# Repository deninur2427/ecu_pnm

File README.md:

# PNM Engine Control Planning

Custom Engine Control Unit for LPG

## Planning

- [X] Ngobrol Rencana

### Input

- [ ] Crankshaft Position Sensor
    - [ ] Pasang Gigi. Rencana Penempatan 12-1 Crank Tooth:

    - [ ] Cetak Crank Teeth 12-1. Diameter Poros 22mm. Contoh:

    - [ ] Alternatif akrilik. Desain (tebal 2mm atau 3mm) untuk 24-1:

    - [ ] Pasang Sensor Gigi. Rencana Sensor: Opto Interruptor: [Tokopedia](https://www.tokopedia.com/xurve-store/fc-03-ir-infrared-speed-kecepatan-sensor-photo-opto-interruptor)

- [ ] Trottle Position Sensor
    - [ ] Pemasangan. Dimana dekat mesin karena tidak terkoneksi dengan mekanik intake
    - [ ] Pembelian Sensor TPS: [Tokopedia](https://www.tokopedia.com/primacave/terbaru-sensor-tps-throttle-position-sensor-beat-fi-vario-125-thalland)

- [ ] Optimasi
    - [ ] Sensor Temperature (Tentative)
    - [ ] CO2 Sensor. Rencana [Tokopedia](https://www.tokopedia.com/amanahotopart/sensor-oxygen-honda-jazz-city-belakang-oksigen-co2-o2-copotan-asli-ori)

### Output

- [ ] Intake
    - [ ] Injector. Rencana [Tokopedia](https://www.tokopedia.com/sumahonda/injector-assy-fuel-pcx-150-k97-vario-150-esp-16450k59a11)
    - [ ] Pemasangan depan Inlet tanpa klep pengatur udara:

- [ ] Spark Plug
    - [ ] Coil. Rencana [Tokopedia](https://www.tokopedia.com/lestarimotor2/coil-koil-scoopy-esp-scoopy-fi-injeksi-30510-k16-a01-asli-ahm)
    - [ ] Cop Busi [Tokopedia](https://www.tokopedia.com/azkamotor99/canglong-tutup-cop-busi-grand-supra-x-x-125-legenda-revo-kharisma)
    - [ ] Plug telah tersedia

- [ ] Aki. Alternator dan Kiprok tidak ada di Mesin
    - [x] Charger Aki tersedia
    - [ ] Jepit Aki dan Wiring nya

### PCB

- [ ] Drafting
    - [ ] Single Cylinder
        - [ ] Standalone PCB
        - [x] Nucleo Based
            - [x] F103RB

- [x] Rencana Anggaran Total

### Update Kegiatan

- Tanggal 31 Juli 2023: [Catatan](https://github.com/deninur2427/ecu_pnm/blob/main/docs/notes/tes_31072023.md)
- Tanggal 24 Agustus 2023: [Catatan](https://github.com/deninur2427/ecu_pnm/blob/main/docs/notes/tes_24082023.md)
- Tanggal 19 September 2023: [Catatan](https://github.com/deninur2427/ecu_pnm/blob/main/docs/notes/tes_19092023.md)

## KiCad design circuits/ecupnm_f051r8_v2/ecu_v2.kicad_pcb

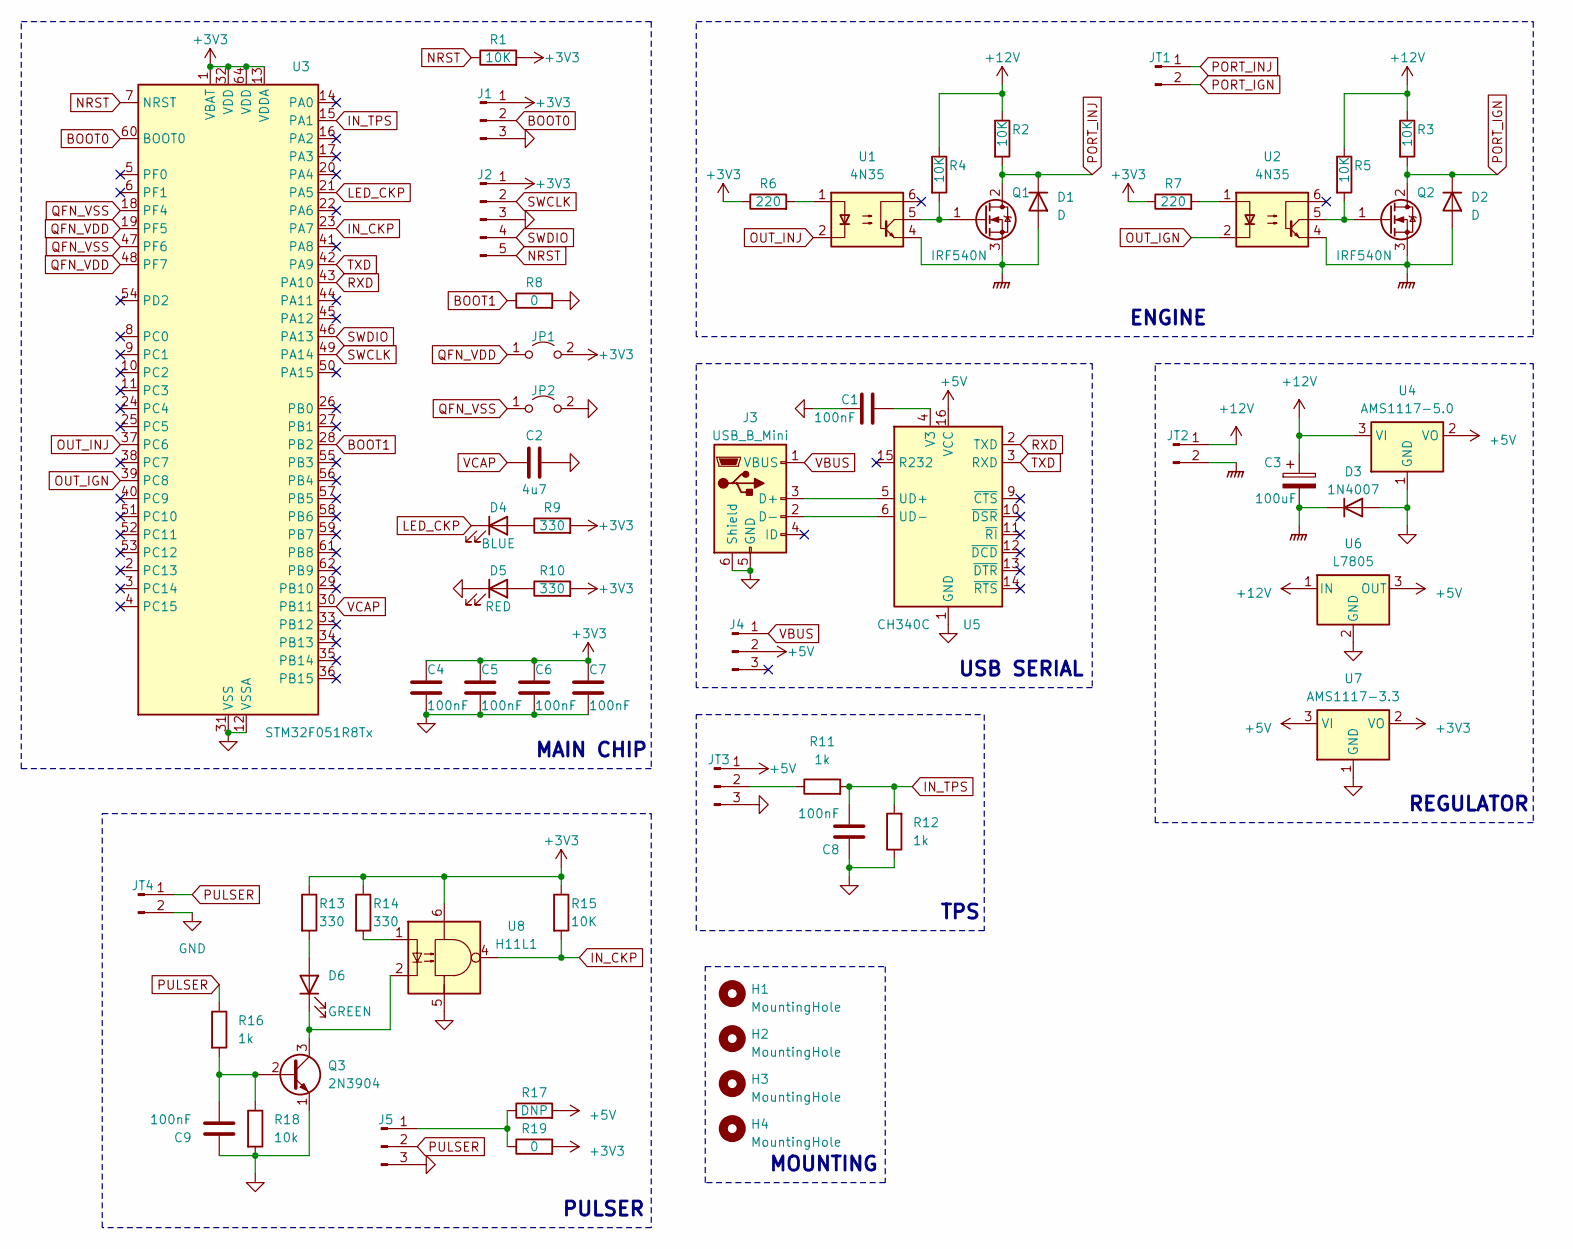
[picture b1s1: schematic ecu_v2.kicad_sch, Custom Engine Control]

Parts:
C1, C4, C5, C6, C7, C8, C9: 100nF; C_0805_2012Metric_Pad1.18x1.45mm_HandSolder
C2: 4u7; C_0805_2012Metric_Pad1.18x1.45mm_HandSolder
C3: 100uF; CP_Radial_D4.0mm_P2.00mm
D1, D2: D; D_DO-15_P10.16mm_Horizontal
D3: 1N4007; D_DO-41_SOD81_P10.16mm_Horizontal
D4: BLUE; LED_0805_2012Metric_Pad1.15x1.40mm_HandSolder
D5: RED; LED_0805_2012Metric_Pad1.15x1.40mm_HandSolder
D6: GREEN; LED_0805_2012Metric_Pad1.15x1.40mm_HandSolder
H1, H2, H3, H4: MountingHole; MountingHole_2.2mm_M2
J1, J4, J5: Conn_01x03_Pin; PinHeader_1x03_P2.54mm_Vertical
J2: Conn_01x05_Pin; PinHeader_1x05_P2.54mm_Vertical
J3: USB_B_Mini; USB_Mini-B_Wuerth_65100516121_Horizontal
JP1, JP2: Jumper_2_Open; SolderJumper-2_P1.3mm_Open_RoundedPad1.0x1.5mm
JT1, JT2, JT4: Conn_01x02_Pin; TerminalBlock_Altech_AK300-2_P5.00mm
JT3: Conn_01x03_Pin; TerminalBlock_Altech_AK300-3_P5.00mm
Q1, Q2: IRF540N; TO-220-3_Vertical
Q3: 2N3904; TO-92_Inline
R1, R2, R3, R4, R5, R15: 10K; R_0805_2012Metric_Pad1.20x1.40mm_HandSolder
R6, R7: 220; R_0805_2012Metric_Pad1.20x1.40mm_HandSolder
R8, R19: 0; R_0805_2012Metric_Pad1.20x1.40mm_HandSolder
R9, R10, R13, R14: 330; R_0805_2012Metric_Pad1.20x1.40mm_HandSolder
R11, R12, R16: 1k; R_0805_2012Metric_Pad1.20x1.40mm_HandSolder
R17: DNP; R_0805_2012Metric_Pad1.20x1.40mm_HandSolder
R18: 10k; R_0805_2012Metric_Pad1.20x1.40mm_HandSolder
U1, U2: 4N35; DIP-6_W7.62mm
U3: STM32F051R8Tx; LQFP-64_10x10mm_P0.5mm
U4: AMS1117-5.0; SOT-223-3_TabPin2
U5: CH340C; SOIC-16_3.9x9.9mm_P1.27mm
U6: L7805; TO-220-3_Vertical
U7: AMS1117-3.3; SOT-223-3_TabPin2
U8: H11L1; DIP-6_W7.62mm

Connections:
+3V3: C4.1, C5.1, C6.1, C7.1, J1.1, J2.1, JP1.2 (B), R1.2, R6.1, R7.1, R9.2, R10.2, R13.1, R14.1, R15.1, R19.2, U3.1 (VBAT), U3.13 (VDDA), U3.32 (VDD), U3.64 (VDD), U7.2 (VO), U8.6
+5V: J4.2, JT3.1, R17.2, U4.2 (VO), U5.16 (VCC), U6.3 (OUT), U7.3 (VI)
+12V: C3.1, JT2.1, R2.1, R3.1, R4.1, R5.1, U4.3 (VI), U6.1 (IN)
BOOT0: J1.2, U3.60 (BOOT0)
BOOT1: R8.1, U3.28 (PB2)
GND: C1.2, C2.2, C4.2, C5.2, C6.2, C7.2, C8.1, C9.1, D3.2 (A), D5.1 (K), J1.3, J2.3, J3.5 (GND), J3.6 (Shield), J5.3, JP2.2 (B), JT3.3, JT4.2, Q3.1 (E), R8.2, R12.1, R18.2, U3.12 (VSSA), U3.31 (VSS), U3.63 (VSS), U4.1 (GND), U5.1 (GND), U6.2 (GND), U7.1 (GND), U8.5
GNDPWR: C3.2, D1.2 (A), D2.2 (A), D3.1 (K), JT2.2, Q1.3 (S), Q2.3 (S), U1.4, U2.4
IN_CKP: R15.2, U3.23 (PA7), U8.4
IN_TPS: C8.2, R11.2, R12.2, U3.15 (PA1)
LED_CKP: D4.1 (K), U3.21 (PA5)
NRST: J2.5, R1.1, U3.7 (NRST)
unnamed: D4.2 (A), R9.1
unnamed: D5.2 (A), R10.1
unnamed: D6.2 (A), R13.2
unnamed: D6.1 (K), Q3.3 (C), U8.2
unnamed: J3.3 (D+), U5.5 (UD+)
unnamed: J3.2 (D-), U5.6 (UD-)
unnamed: J5.1, R17.1, R19.1
unnamed: JT3.2, R11.1
unnamed: Q1.1 (G), R4.2, U1.5
unnamed: Q2.1 (G), R5.2, U2.5
unnamed: C9.2, Q3.2 (B), R16.2, R18.1
unnamed: R6.2, U1.1
unnamed: R7.2, U2.1
unnamed: R14.2, U8.1
unnamed: C1.1, U5.4 (V3)
OUT_IGN: U2.2, U3.39 (PC8)
OUT_INJ: U1.2, U3.37 (PC6)
PORT_IGN: D2.1 (K), JT1.2, Q2.2 (D), R3.2
PORT_INJ: D1.1 (K), JT1.1, Q1.2 (D), R2.2
PULSER: J5.2, JT4.1, R16.1
QFN_VDD: JP1.1 (A), U3.19 (PF5), U3.48 (PF7)
QFN_VSS: JP2.1 (A), U3.18 (PF4), U3.47 (PF6)
RXD: U3.43 (PA10), U5.2 (TXD)
SWCLK: J2.2, U3.49 (PA14)
SWDIO: J2.4, U3.46 (PA13)
TXD: U3.42 (PA9), U5.3 (RXD)
VBUS: J3.1 (VBUS), J4.1
VCAP: C2.1, U3.30 (PB11)

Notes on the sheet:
REGULATOR
ENGINE
MAIN CHIP
TPS
PULSER
MOUNTING
USB SERIAL

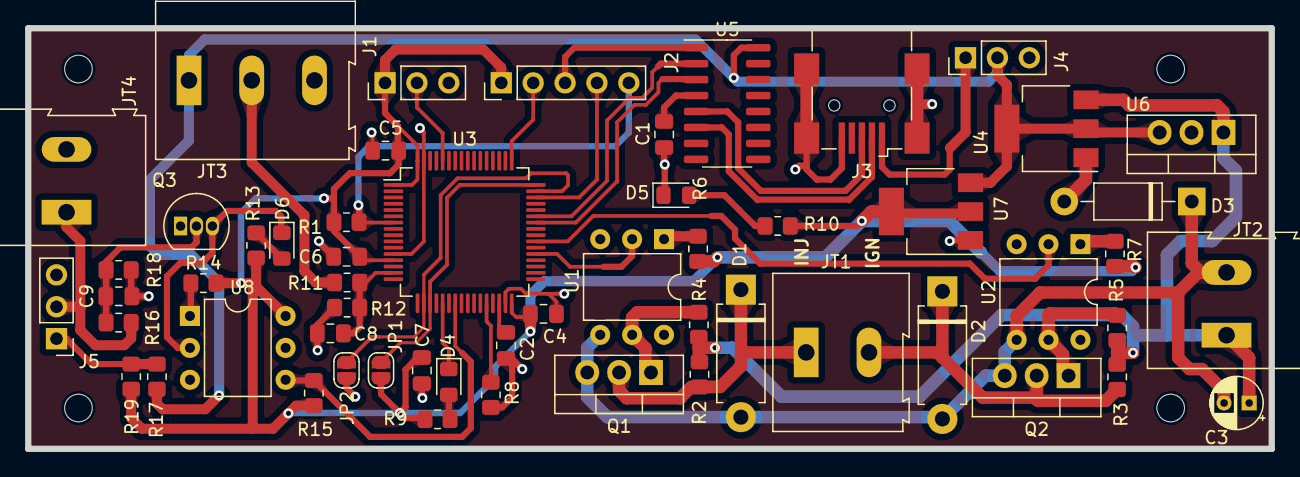
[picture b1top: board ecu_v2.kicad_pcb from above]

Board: 2 copper layers, 99.1 x 33.5 mm, 60 parts (0 on the bottom side), 39 nets.

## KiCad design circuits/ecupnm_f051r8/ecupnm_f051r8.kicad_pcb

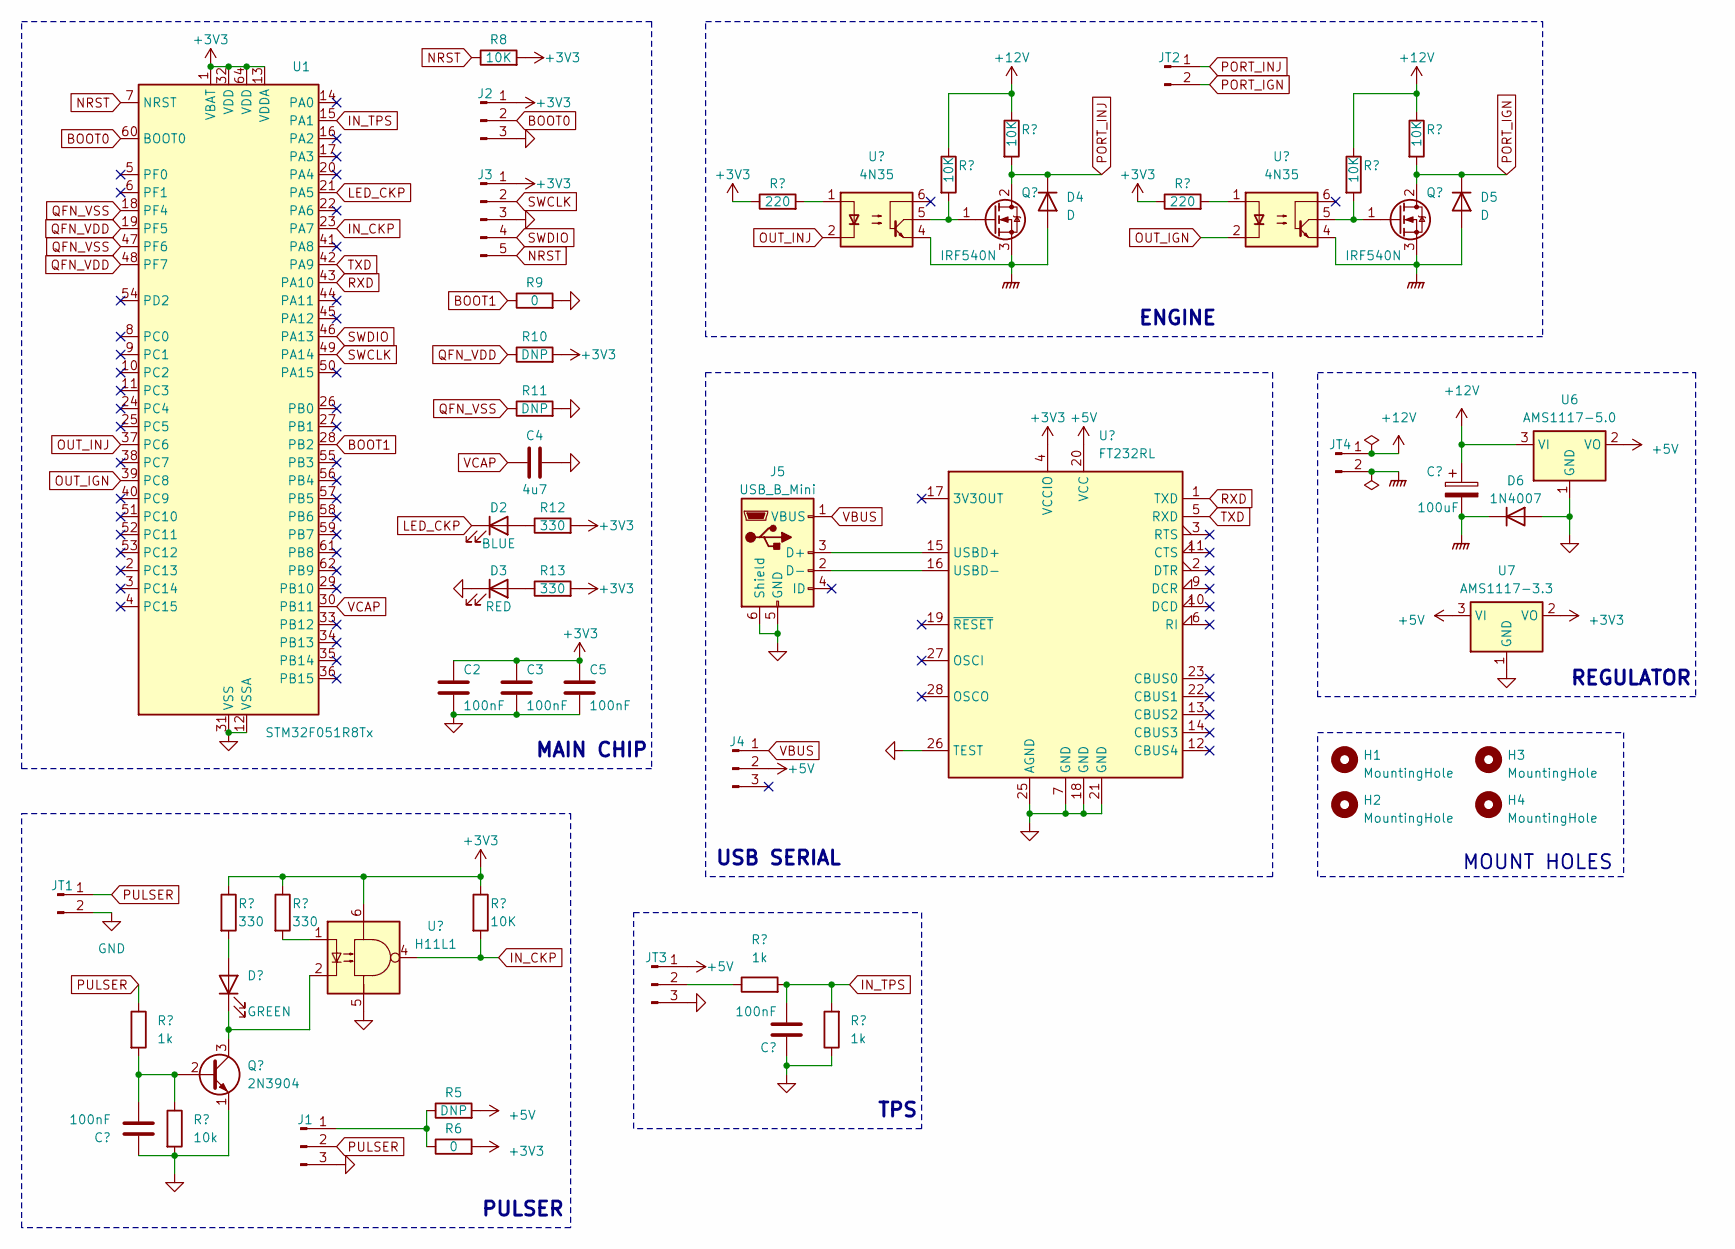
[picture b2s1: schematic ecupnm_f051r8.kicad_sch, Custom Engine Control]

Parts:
C1, C2, C3, C5, C6: 100nF; C_0805_2012Metric_Pad1.18x1.45mm_HandSolder
C4: 4u7; C_0805_2012Metric_Pad1.18x1.45mm_HandSolder
C7: 100uF; CP_Radial_D4.0mm_P2.00mm
D1: GREEN; LED_0805_2012Metric_Pad1.15x1.40mm_HandSolder
D2: BLUE; LED_0805_2012Metric_Pad1.15x1.40mm_HandSolder
D3: RED; LED_0805_2012Metric_Pad1.15x1.40mm_HandSolder
D4, D5: D; D_DO-15_P10.16mm_Horizontal
D6: 1N4007; D_DO-41_SOD81_P10.16mm_Horizontal
H1, H2, H3, H4: MountingHole; MountingHole_2.5mm
J1, J2, J4: Conn_01x03_Pin; PinHeader_1x03_P2.54mm_Vertical
J3: Conn_01x05_Pin; PinHeader_1x05_P2.54mm_Vertical
J5: USB_B_Mini; USB_Mini-B_Wuerth_65100516121_Horizontal
JT1, JT2, JT4: Conn_01x02_Pin; TerminalBlock_Altech_AK300-2_P5.00mm
JT3: Conn_01x03_Pin; TerminalBlock_Altech_AK300-3_P5.00mm
Q1: 2N3904; TO-92_Inline
Q2, Q3: IRF540N; TO-220-3_Vertical
R1, R20, R21: 1k; R_0805_2012Metric_Pad1.20x1.40mm_HandSolder
R2: 10k; R_0805_2012Metric_Pad1.20x1.40mm_HandSolder
R3, R4, R12, R13: 330; R_0805_2012Metric_Pad1.20x1.40mm_HandSolder
R5, R10, R11: DNP; R_0805_2012Metric_Pad1.20x1.40mm_HandSolder
R6, R9: 0; R_0805_2012Metric_Pad1.20x1.40mm_HandSolder
R7, R8, R15, R16, R18, R19: 10K; R_0805_2012Metric_Pad1.20x1.40mm_HandSolder
R14, R17: 220; R_0805_2012Metric_Pad1.20x1.40mm_HandSolder
U1: STM32F051R8Tx; LQFP-64_10x10mm_P0.5mm
U2: H11L1; DIP-6_W7.62mm
U3, U5: 4N35; DIP-6_W7.62mm
U4: FT232RL; SSOP-28_5.3x10.2mm_P0.65mm
U6: AMS1117-5.0; SOT-223-3_TabPin2
U7: AMS1117-3.3; SOT-223-3_TabPin2

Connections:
+3V3: C2.1, C3.1, C5.1, J2.1, J3.1, R3.1, R4.1, R6.2, R7.1, R8.2, R10.2, R12.2, R13.2, R14.1, R17.1, U1.1 (VBAT), U1.13 (VDDA), U1.32 (VDD), U1.64 (VDD), U2.6, U4.4 (VCCIO), U7.2 (VO)
+5V: J4.2, JT3.1, R5.2, U4.20 (VCC), U6.2 (VO), U7.3 (VI)
+12V: C7.1, JT4.1, R15.1, R16.1, R18.1, R19.1, U6.3 (VI)
BOOT0: J2.2, U1.60 (BOOT0)
BOOT1: R9.1, U1.28 (PB2)
GND: C1.1, C2.2, C3.2, C4.2, C5.2, C6.1, D3.1 (K), D6.2 (A), J1.3, J2.3, J3.3, J5.5 (GND), J5.6 (Shield), JT1.2, JT3.3, Q1.1 (E), R2.2, R9.2, R11.2, R21.1, U1.12 (VSSA), U1.31 (VSS), U1.63 (VSS), U2.5, U4.7 (GND), U4.18 (GND), U4.21 (GND), U4.25 (AGND), U4.26 (TEST), U6.1 (GND), U7.1 (GND)
GNDPWR: C7.2, D4.2 (A), D5.2 (A), D6.1 (K), JT4.2, Q2.3 (S), Q3.3 (S), U3.4, U5.4
IN_CKP: R7.2, U1.23 (PA7), U2.4
IN_TPS: C6.2, R20.2, R21.2, U1.15 (PA1)
LED_CKP: D2.1 (K), U1.21 (PA5)
NRST: J3.5, R8.1, U1.7 (NRST)
unnamed: D1.2 (A), R3.2
unnamed: D1.1 (K), Q1.3 (C), U2.2
unnamed: D2.2 (A), R12.1
unnamed: D3.2 (A), R13.1
unnamed: J1.1, R5.1, R6.1
unnamed: J5.3 (D+), U4.15 (USBD+)
unnamed: J5.2 (D-), U4.16 (USBD-)
unnamed: JT3.2, R20.1
unnamed: C1.2, Q1.2 (B), R1.2, R2.1
unnamed: Q2.1 (G), R15.2, U3.5
unnamed: Q3.1 (G), R18.2, U5.5
unnamed: R4.2, U2.1
unnamed: R14.2, U3.1
unnamed: R17.2, U5.1
OUT_IGN: U1.39 (PC8), U5.2
OUT_INJ: U1.37 (PC6), U3.2
PORT_IGN: D5.1 (K), JT2.2, Q3.2 (D), R19.2
PORT_INJ: D4.1 (K), JT2.1, Q2.2 (D), R16.2
PULSER: J1.2, JT1.1, R1.1
QFN_VDD: R10.1, U1.19 (PF5), U1.48 (PF7)
QFN_VSS: R11.1, U1.18 (PF4), U1.47 (PF6)
RXD: U1.43 (PA10), U4.1 (TXD)
SWCLK: J3.2, U1.49 (PA14)
SWDIO: J3.4, U1.46 (PA13)
TXD: U1.42 (PA9), U4.5 (RXD)
VBUS: J4.1, J5.1 (VBUS)
VCAP: C4.1, U1.30 (PB11)

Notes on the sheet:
TPS
MOUNT HOLES
REGULATOR
USB SERIAL
MAIN CHIP
PULSER
ENGINE

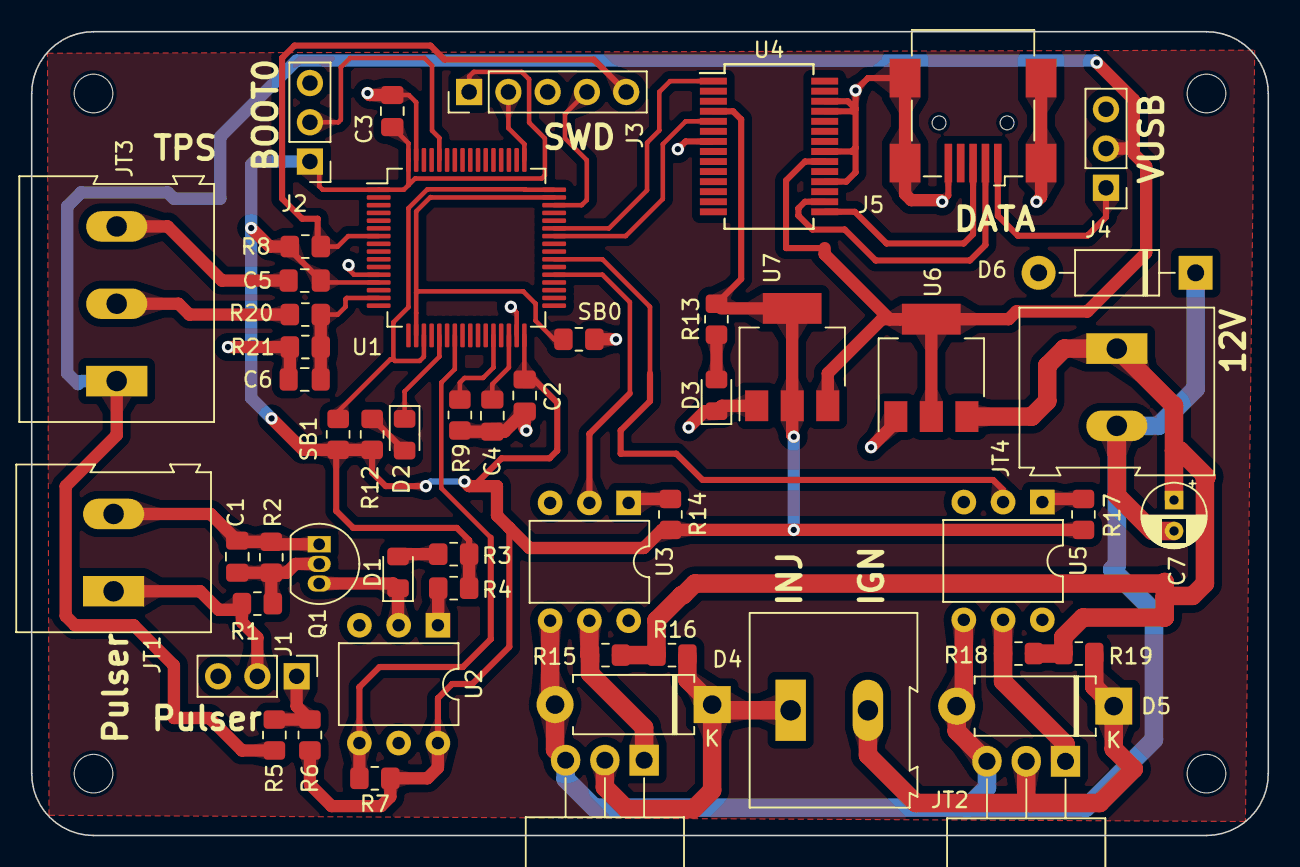
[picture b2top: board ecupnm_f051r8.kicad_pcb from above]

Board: 2 copper layers, 80.0 x 52.0 mm, 57 parts (0 on the bottom side), 38 nets.

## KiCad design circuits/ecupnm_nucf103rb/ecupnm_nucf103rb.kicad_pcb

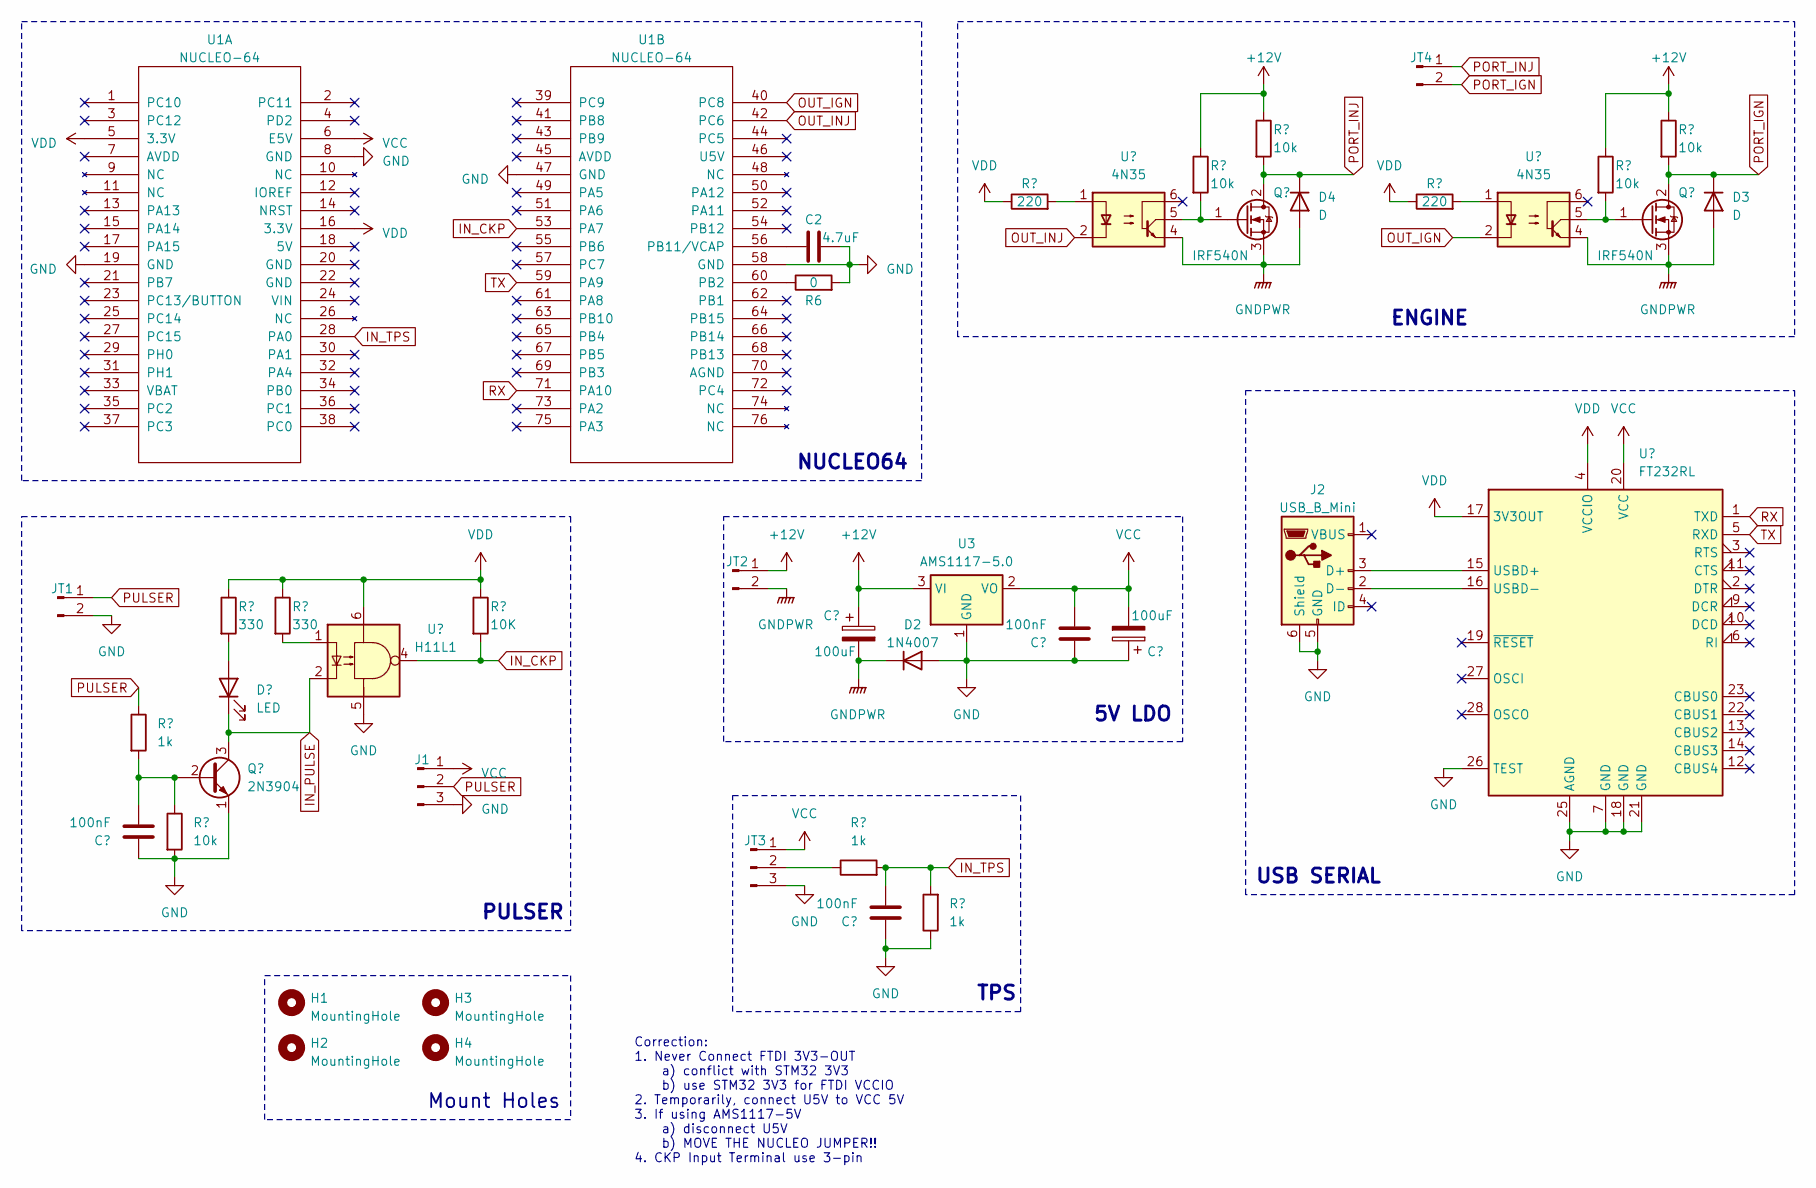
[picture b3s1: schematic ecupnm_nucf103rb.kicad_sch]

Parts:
C1, C4, C5: 100nF; C_1206_3216Metric_Pad1.33x1.80mm_HandSolder
C2: 4.7uF; C_1206_3216Metric_Pad1.33x1.80mm_HandSolder
C3, C6: 100uF; CP_Radial_D7.5mm_P2.50mm
D1: LED; LED_1206_3216Metric_Pad1.42x1.75mm_HandSolder
D2: 1N4007; D_DO-41_SOD81_P10.16mm_Horizontal
D3, D4: D; D_DO-15_P10.16mm_Horizontal
H1, H2, H3, H4: MountingHole; MountingHole_2.5mm
J1: Conn_01x03_Pin; PinHeader_1x03_P2.54mm_Vertical
J2: USB_B_Mini; USB_Mini-B_Wuerth_65100516121_Horizontal
JT1, JT2, JT4: Conn_01x02_Pin; TerminalBlock_Altech_AK300-2_P5.00mm
JT3: Conn_01x03_Pin; TerminalBlock_Altech_AK300-3_P5.00mm
Q1: 2N3904; TO-92_Inline
Q2, Q3: IRF540N; TO-220-3_Horizontal_TabDown
R1, R7, R8: 1k; R_1206_3216Metric_Pad1.30x1.75mm_HandSolder
R2, R10, R11, R13, R14: 10k; R_1206_3216Metric_Pad1.30x1.75mm_HandSolder
R3, R4: 330; R_1206_3216Metric_Pad1.30x1.75mm_HandSolder
R5: 10K; R_1206_3216Metric_Pad1.30x1.75mm_HandSolder
R6: 0; R_1206_3216Metric_Pad1.30x1.75mm_HandSolder
R9, R12: 220; R_1206_3216Metric_Pad1.30x1.75mm_HandSolder
U1: NUCLEO-64; Nucleo-64
U2: H11L1; DIP-6_W7.62mm
U3: AMS1117-5.0; SOT-223-3_TabPin2
U4, U5: 4N35; DIP-6_W7.62mm
U6: FT232RL; SSOP-28_5.3x10.2mm_P0.65mm

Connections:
+12V: C3.1, JT2.1, R10.1, R11.1, R13.1, R14.1, U3.3 (VI)
GND: C1.1, C2.2, C4.1, C5.1, C6.1, D2.2 (A), J1.3, J2.5 (GND), J2.6 (Shield), JT1.2, JT3.3, Q1.1 (E), R2.2, R6.2, R8.1, U1.8 (GND), U1.19 (GND), U1.47 (GND), U1.58 (GND), U2.5, U3.1 (GND), U6.7 (GND), U6.18 (GND), U6.21 (GND), U6.25 (AGND), U6.26 (TEST)
GNDPWR: C3.2, D2.1 (K), D3.2 (A), D4.2 (A), JT2.2, Q2.3 (S), Q3.3 (S), U4.4, U5.4
IN_CKP: R5.2, U1.53 (PA7), U2.4
IN_PULSE: D1.1 (K), Q1.3 (C), U2.2
IN_TPS: C4.2, R7.2, R8.2, U1.28 (PA0)
unnamed: D1.2 (A), R3.2
unnamed: J2.3 (D+), U6.15 (USBD+)
unnamed: J2.2 (D-), U6.16 (USBD-)
unnamed: JT3.2, R7.1
unnamed: C1.2, Q1.2 (B), R1.2, R2.1
unnamed: Q2.1 (G), R10.2, U4.5
unnamed: Q3.1 (G), R13.2, U5.5
unnamed: R4.2, U2.1
unnamed: R9.2, U4.1
unnamed: R12.2, U5.1
unnamed: R6.1, U1.60 (PB2)
unnamed: C2.1, U1.56 (PB11/VCAP)
OUT_IGN: U1.40 (PC8), U5.2
OUT_INJ: U1.42 (PC6), U4.2
PORT_IGN: D3.1 (K), JT4.2, Q3.2 (D), R14.2
PORT_INJ: D4.1 (K), JT4.1, Q2.2 (D), R11.2
PULSER: J1.2, JT1.1, R1.1
RX: U1.71 (PA10), U6.1 (TXD)
TX: U1.59 (PA9), U6.5 (RXD)
VCC: C5.2, C6.2, J1.1, JT3.1, U1.6 (E5V), U3.2 (VO), U6.20 (VCC)
VDD: R3.1, R4.1, R5.1, R9.1, R12.1, U1.5 (3.3V), U1.16 (3.3V), U2.6, U6.4 (VCCIO), U6.17 (3V3OUT)

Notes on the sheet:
Mount Holes
NUCLEO64
TPS
5V LDO
USB SERIAL
PULSER
ENGINE
Correction: 1. Never Connect FTDI 3V3-OUT a) conflict with STM32 3V3 b) use STM32 3V3 for FTDI VCCIO 2. Temporarily, connect U5V to VCC 5V 3. If using AMS1117-5V a) disconnect U5V b) MOVE THE NUCLEO JUMPER!! 4. CKP Input Terminal use 3-pin

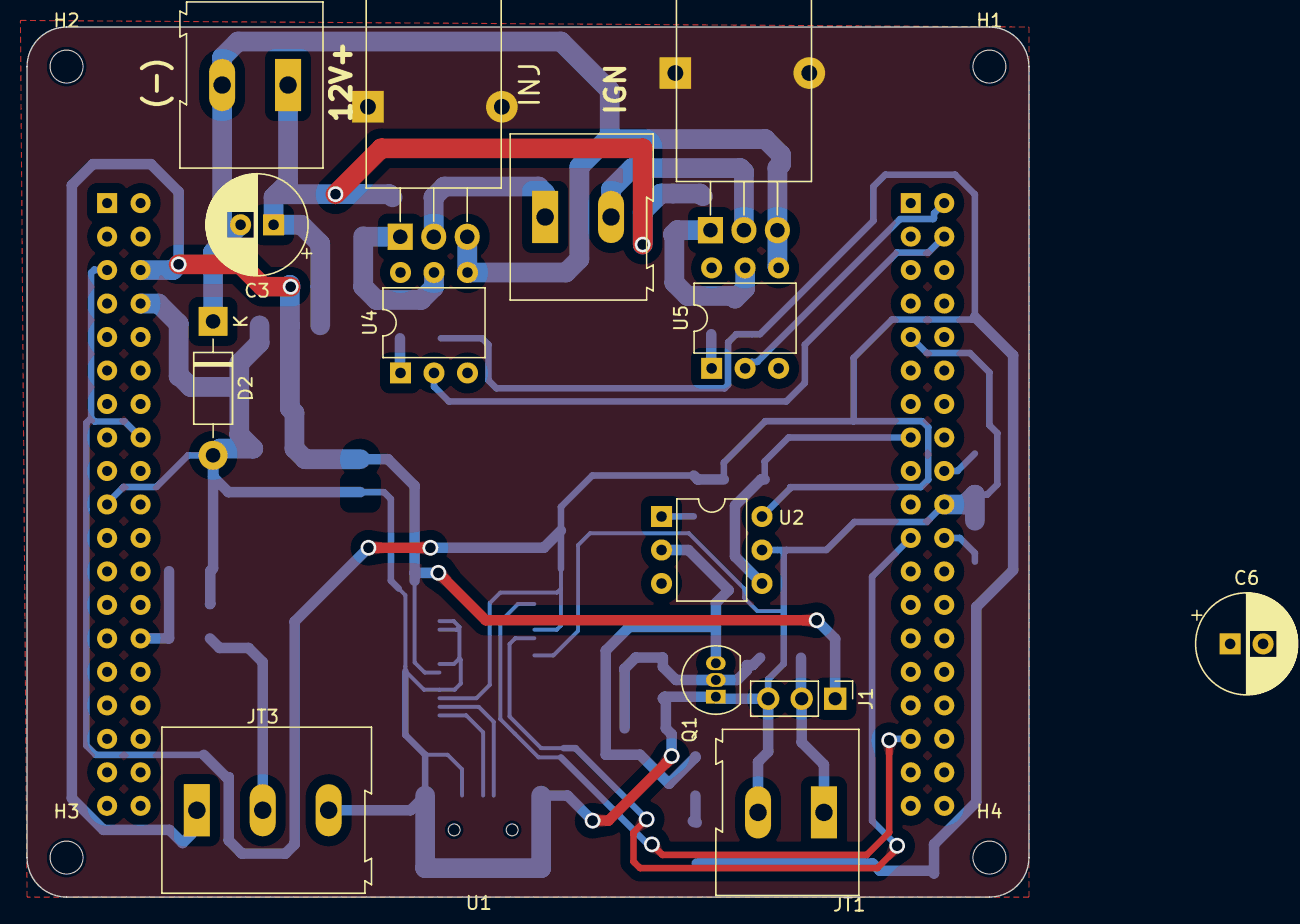
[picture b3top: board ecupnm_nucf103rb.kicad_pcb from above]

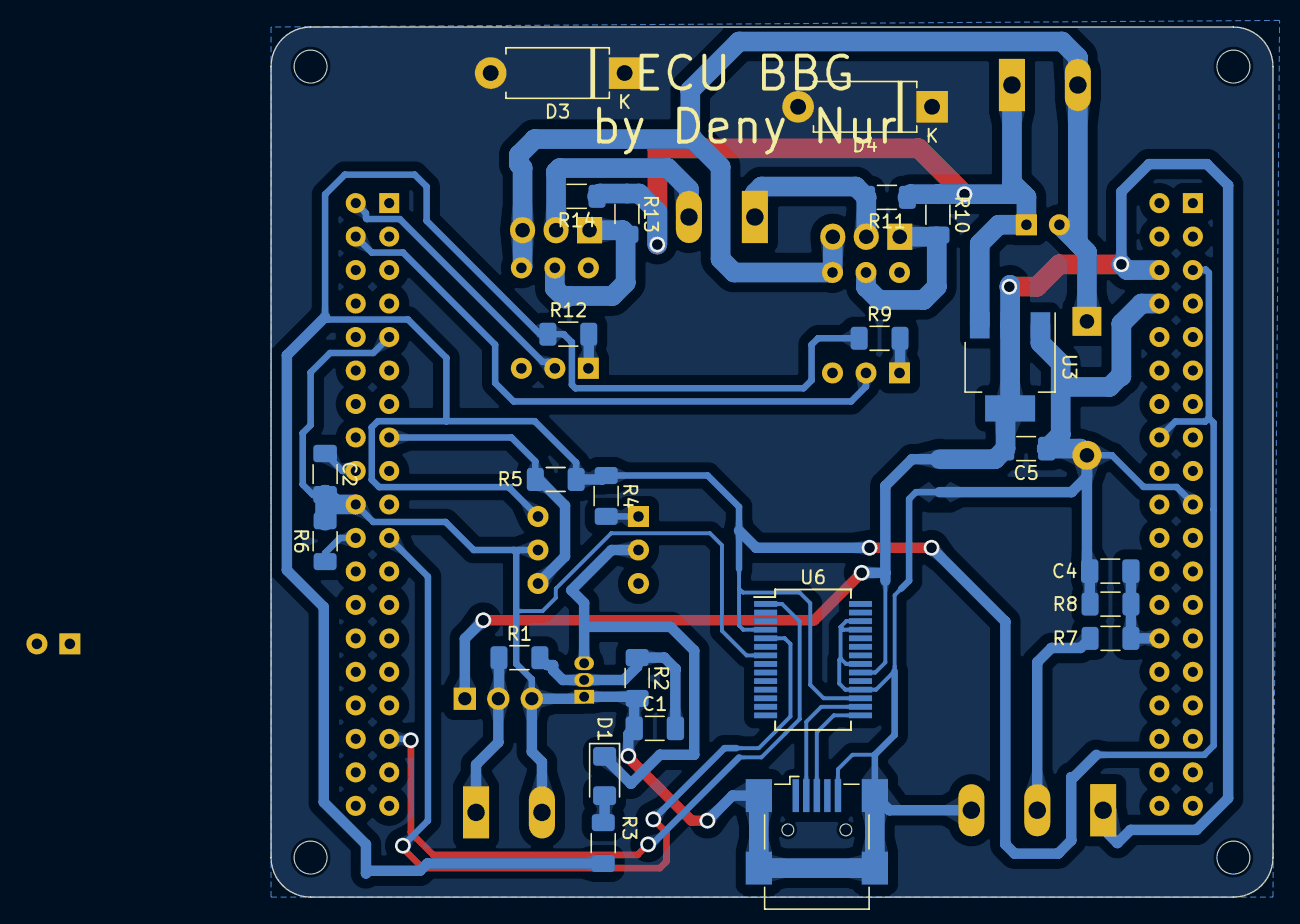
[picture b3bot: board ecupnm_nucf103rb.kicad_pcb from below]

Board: 2 copper layers, 76.0 x 66.0 mm, 43 parts (24 on the bottom side), 27 nets.

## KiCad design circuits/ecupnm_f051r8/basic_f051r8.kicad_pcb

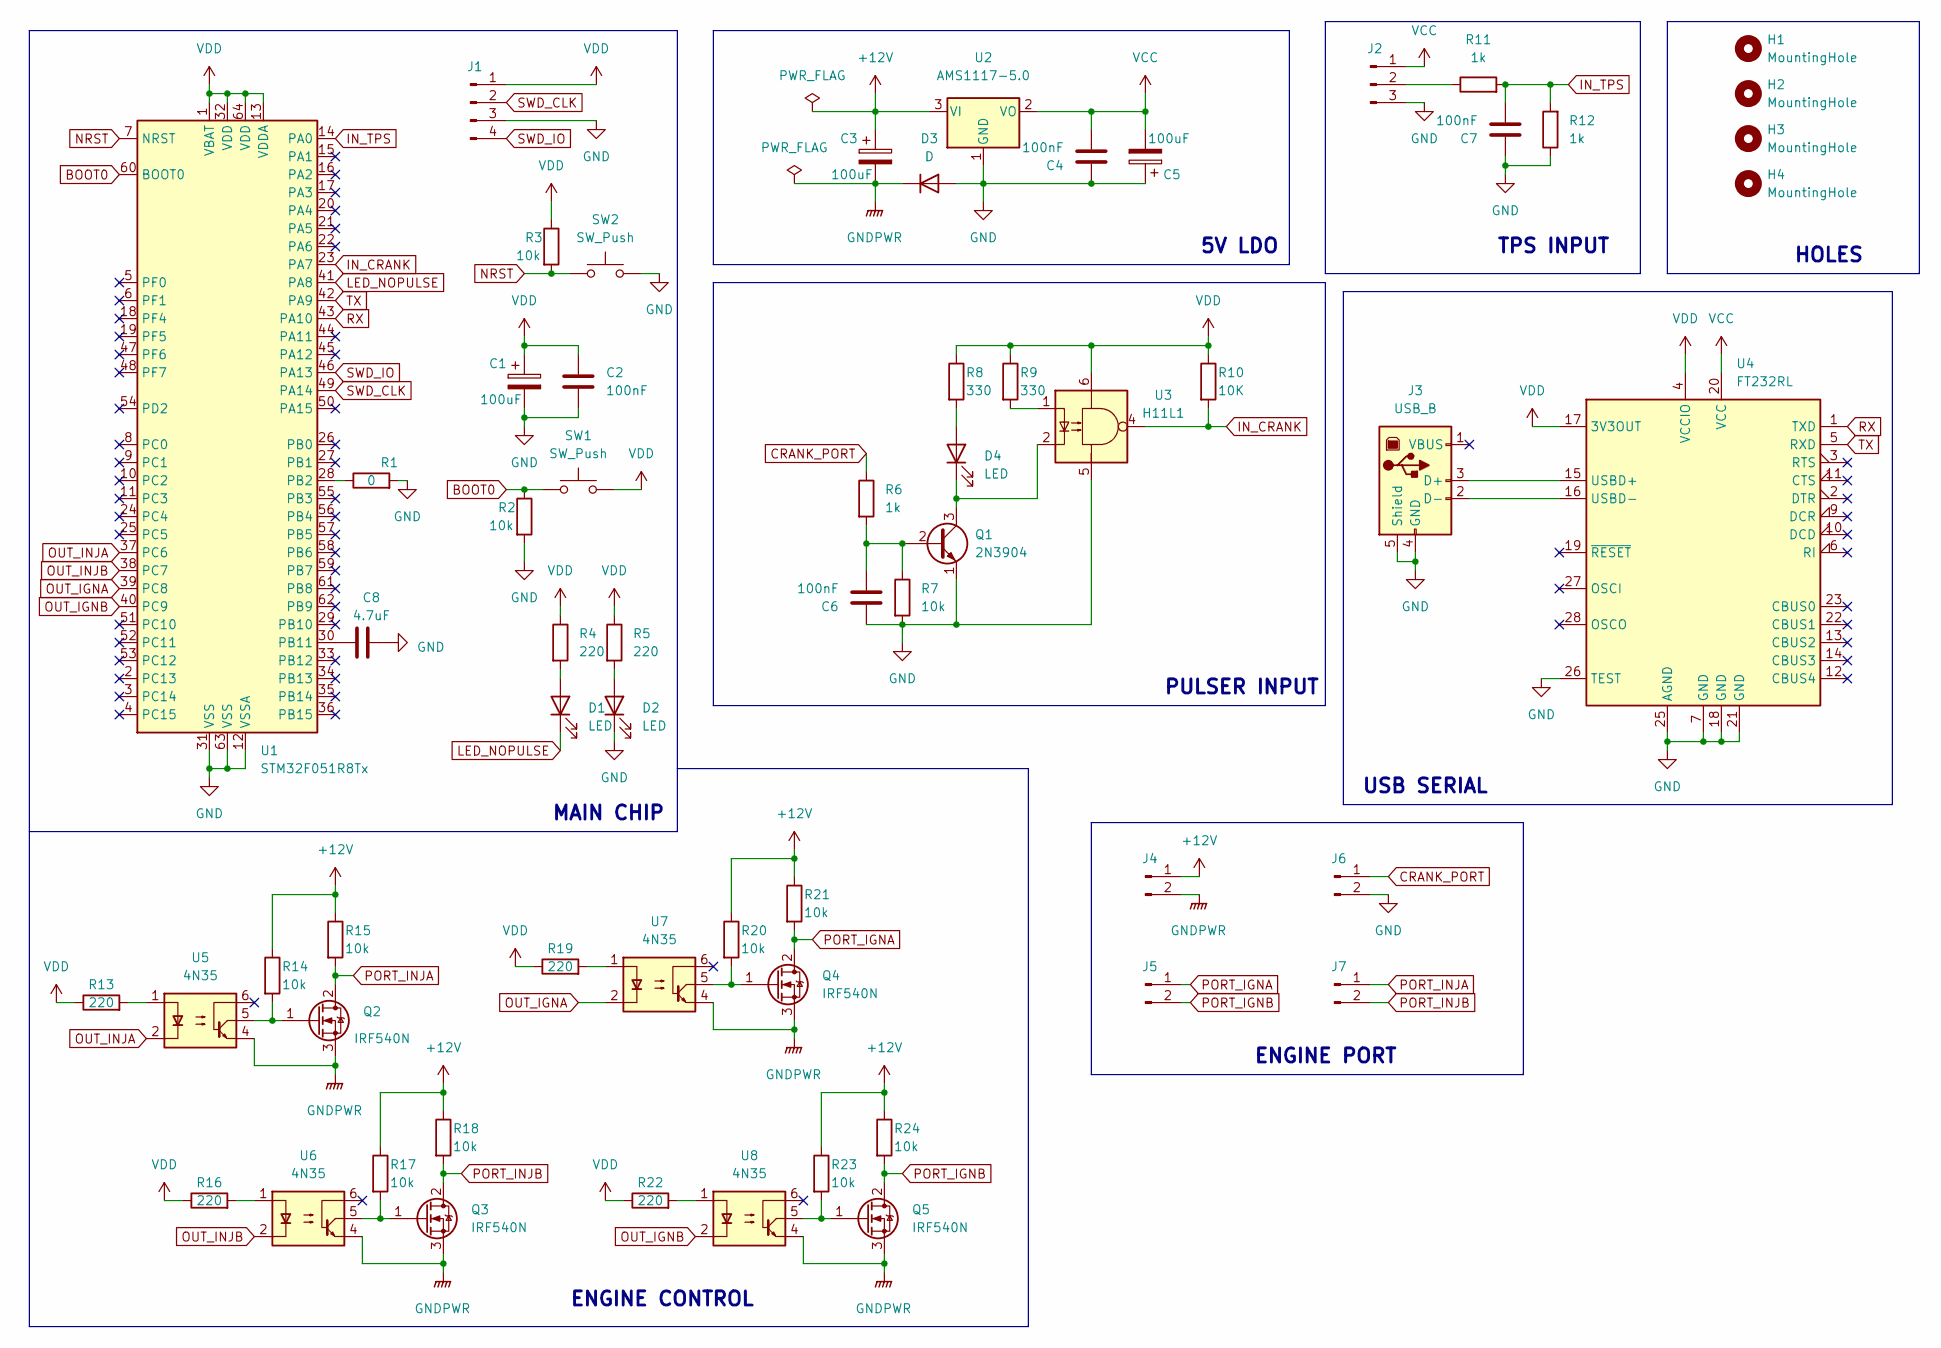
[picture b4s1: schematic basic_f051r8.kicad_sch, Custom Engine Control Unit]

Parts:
C1, C5: 100uF; C_Elec_4x5.4
C2, C4, C6, C7: 100nF; C_0805_2012Metric_Pad1.18x1.45mm_HandSolder
C3: 100uF; C_0805_2012Metric_Pad1.18x1.45mm_HandSolder
C8: 4.7uF
D1, D2, D4: LED; LED_0805_2012Metric_Pad1.15x1.40mm_HandSolder
D3: D; D_SMA-SMB_Universal_Handsoldering
H1, H2, H3, H4: MountingHole; MountingHole_2.5mm_Pad
J1: Conn_01x04_Male; PinHeader_1x04_P2.54mm_Vertical
J2: Conn_01x03_Male; TerminalBlock_Altech_AK300-3_P5.00mm
J3: USB_B; USB_B_Lumberg_2411_02_Horizontal
J4, J5, J6, J7: Conn_01x02_Male; TerminalBlock_Altech_AK300-2_P5.00mm
Q1: 2N3904; TO-92_Inline
Q2, Q3, Q4, Q5: IRF540N; TO-220-3_Horizontal_TabUp
R1: 0; R_0805_2012Metric_Pad1.20x1.40mm_HandSolder
R2, R3, R7, R14, R15, R17, R18, R20, R21, R23, R24: 10k; R_0805_2012Metric_Pad1.20x1.40mm_HandSolder
R4, R5, R13, R16, R19, R22: 220; R_0805_2012Metric_Pad1.20x1.40mm_HandSolder
R6, R11, R12: 1k; R_0805_2012Metric_Pad1.20x1.40mm_HandSolder
R8, R9: 330; R_0805_2012Metric_Pad1.20x1.40mm_HandSolder
R10: 10K; R_0805_2012Metric_Pad1.20x1.40mm_HandSolder
SW1, SW2: SW_Push; SW_PUSH_6mm
U1: STM32F051R8Tx; LQFP-64_10x10mm_P0.5mm
U2: AMS1117-5.0; SOT-223-3_TabPin2
U3: H11L1; DIP-6_W7.62mm
U4: FT232RL; SSOP-28_5.3x10.2mm_P0.65mm
U5, U6, U7, U8: 4N35; DIP-6_W7.62mm

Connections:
+12V: C3.1, J4.1, R14.1, R15.1, R17.1, R18.1, R20.1, R21.1, R23.1, R24.1, U2.3 (VI)
BOOT0: R2.1, SW1.1, U1.60 (BOOT0)
CRANK_PORT: J6.1, R6.1
GND: C1.2, C2.2, C4.1, C5.1, C6.1, C7.1, C8.2, D2.1 (K), D3.2 (A), J1.3, J2.3, J3.4 (GND), J3.5 (Shield), J6.2, Q1.1 (E), R1.2, R2.2, R7.2, R12.1, SW2.2, U1.12 (VSSA), U1.31 (VSS), U1.63 (VSS), U2.1 (GND), U3.5, U4.7 (GND), U4.18 (GND), U4.21 (GND), U4.25 (AGND), U4.26 (TEST)
GNDPWR: C3.2, D3.1 (K), J4.2, Q2.3 (S), Q3.3 (S), Q4.3 (S), Q5.3 (S), U5.4, U6.4, U7.4, U8.4
IN_CRANK: R10.2, U1.23 (PA7), U3.4
IN_TPS: C7.2, R11.2, R12.2, U1.14 (PA0)
LED_NOPULSE: D1.1 (K), U1.41 (PA8)
NRST: R3.2, SW2.1, U1.7 (NRST)
unnamed: C6.2, Q1.2 (B), R6.2, R7.1
unnamed: C8.1, U1.30 (PB11)
unnamed: D1.2 (A), R4.2
unnamed: D2.2 (A), R5.2
unnamed: D4.1 (K), Q1.3 (C), U3.2
unnamed: D4.2 (A), R8.2
unnamed: J2.2, R11.1
unnamed: Q2.1 (G), R14.2, U5.5
unnamed: Q3.1 (G), R17.2, U6.5
unnamed: Q4.1 (G), R20.2, U7.5
unnamed: Q5.1 (G), R23.2, U8.5
unnamed: R1.1, U1.28 (PB2)
unnamed: R9.2, U3.1
unnamed: R13.2, U5.1
unnamed: R16.2, U6.1
unnamed: R19.2, U7.1
unnamed: R22.2, U8.1
unnamed: J3.3 (D+), U4.15 (USBD+)
unnamed: J3.2 (D-), U4.16 (USBD-)
OUT_IGNA: U1.39 (PC8), U7.2
OUT_IGNB: U1.40 (PC9), U8.2
OUT_INJA: U1.37 (PC6), U5.2
OUT_INJB: U1.38 (PC7), U6.2
PORT_IGNA: J5.1, Q4.2 (D), R21.2
PORT_IGNB: J5.2, Q5.2 (D), R24.2
PORT_INJA: J7.1, Q2.2 (D), R15.2
PORT_INJB: J7.2, Q3.2 (D), R18.2
RX: U1.43 (PA10), U4.1 (TXD)
SWD_CLK: J1.2, U1.49 (PA14)
SWD_IO: J1.4, U1.46 (PA13)
TX: U1.42 (PA9), U4.5 (RXD)
VCC: C4.2, C5.2, J2.1, U2.2 (VO), U4.20 (VCC)
VDD: C1.1, C2.1, J1.1, R3.1, R4.1, R5.1, R8.1, R9.1, R10.1, R13.1, R16.1, R19.1, R22.1, SW1.2, U1.1 (VBAT), U1.13 (VDDA), U1.32 (VDD), U1.64 (VDD), U3.6, U4.4 (VCCIO), U4.17 (3V3OUT)

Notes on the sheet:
PULSER INPUT
MAIN CHIP
5V LDO
USB SERIAL
ENGINE PORT
HOLES
TPS INPUT
ENGINE CONTROL

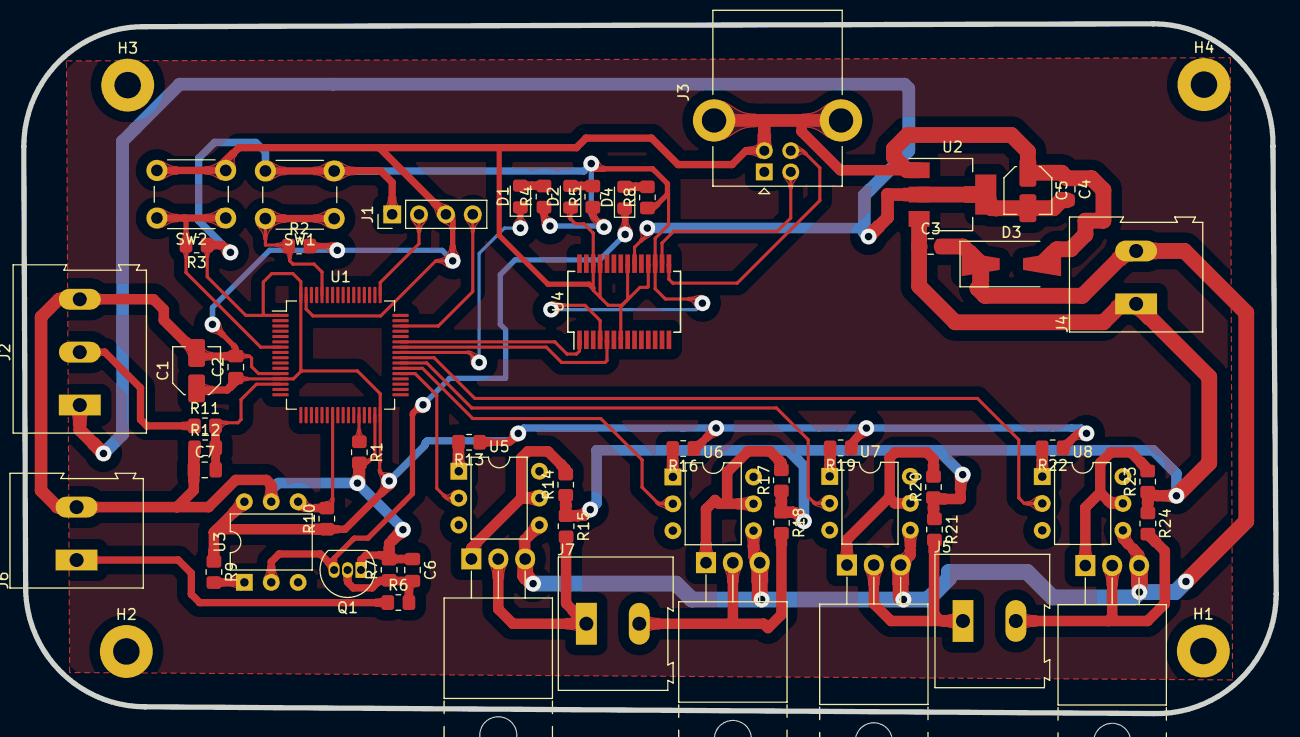
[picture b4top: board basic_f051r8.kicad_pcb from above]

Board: 2 copper layers, 118.4 x 65.2 mm, 61 parts (0 on the bottom side), 41 nets.

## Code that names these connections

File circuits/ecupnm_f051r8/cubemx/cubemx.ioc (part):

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Mcu.Name=STM32F051R8Tx
Mcu.Package=LQFP64
Mcu.UserName=STM32F051R8Tx
PA0.Mode=IN0
PA0.Signal=ADC_IN0
PA10.Mode=Asynchronous
PA10.Signal=USART1_RX
PA13.Mode=Serial_Wire
PA13.Signal=SYS_SWDIO
PA14.Mode=Serial_Wire
PA14.Signal=SYS_SWCLK
PA7.Signal=S_TIM3_CH2
PA8.Signal=GPIO_Output
PA9.Mode=Asynchronous
PA9.Signal=USART1_TX
PC6.Signal=GPIO_Output
PC7.Signal=GPIO_Output
PC8.Signal=GPIO_Output
PC9.Signal=GPIO_Output
board=custom

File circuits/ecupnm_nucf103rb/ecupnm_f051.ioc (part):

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Mcu.Name=STM32F051R8Tx
Mcu.Package=LQFP64
Mcu.UserName=STM32F051R8Tx
PA0.Mode=IN0
PA0.Signal=ADC_IN0
PA10.Mode=Asynchronous
PA10.Signal=USART1_RX
PA13.Mode=Serial_Wire
PA13.Signal=SYS_SWDIO
PA14.Mode=Serial_Wire
PA14.Signal=SYS_SWCLK
PA5.Signal=GPIO_Output
PA7.Signal=S_TIM3_CH2
PA9.Mode=Asynchronous
PA9.Signal=USART1_TX
PB2.Signal=GPIO_Input
PC6.Signal=GPIO_Output
PC8.Signal=GPIO_Output
board=custom
